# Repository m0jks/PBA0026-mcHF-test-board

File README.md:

# PBA0026-mcHF-test-board
# Test board for the mcHF radio by m0nka.

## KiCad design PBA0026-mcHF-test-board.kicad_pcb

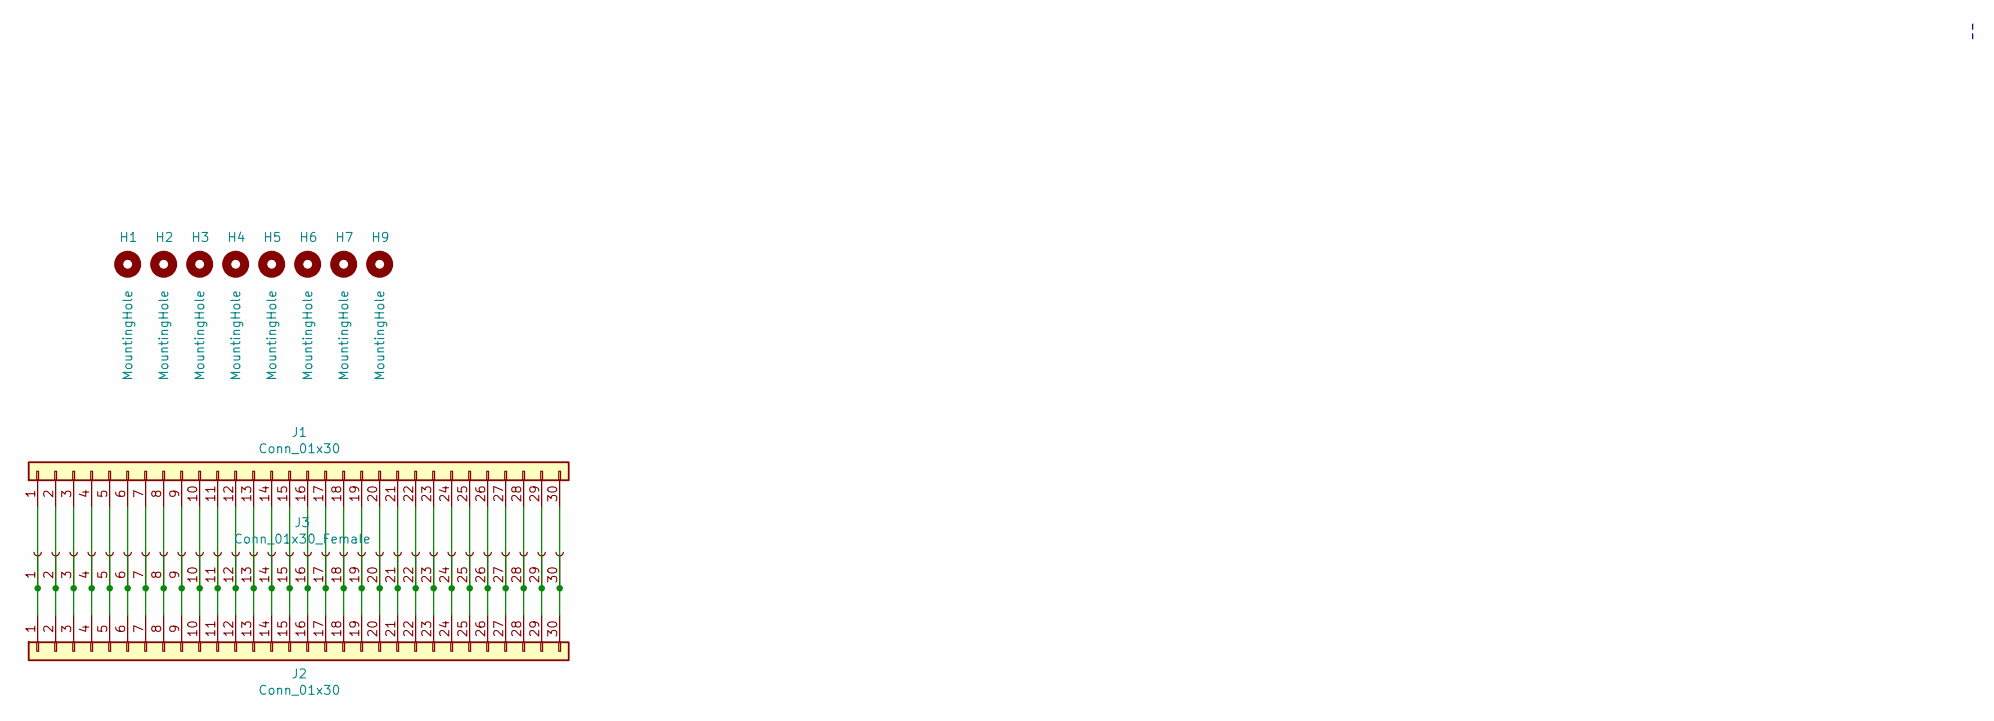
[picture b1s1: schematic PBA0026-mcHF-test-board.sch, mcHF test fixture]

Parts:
H1, H2, H3, H4, H5, H6, H7, H9: MountingHole; MountingHole_3.2mm_M3
J1: Conn_01x30; PinHeader_1x30_P2.54mm_Vertical
J2: Conn_01x30; PinSocket_1x30_P2.54mm_Vertical
J3: Conn_01x30_Female; PinSocket_1x30_P2.54mm_Vertical

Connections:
unnamed: J1.1, J2.1, J3.1
unnamed: J1.2, J2.2, J3.2
unnamed: J1.3, J2.3, J3.3
unnamed: J1.4, J2.4, J3.4
unnamed: J1.5, J2.5, J3.5
unnamed: J1.6, J2.6, J3.6
unnamed: J1.7, J2.7, J3.7
unnamed: J1.8, J2.8, J3.8
unnamed: J1.9, J2.9, J3.9
unnamed: J1.10, J2.10, J3.10
unnamed: J1.11, J2.11, J3.11
unnamed: J1.12, J2.12, J3.12
unnamed: J1.13, J2.13, J3.13
unnamed: J1.14, J2.14, J3.14
unnamed: J1.15, J2.15, J3.15
unnamed: J1.16, J2.16, J3.16
unnamed: J1.17, J2.17, J3.17
unnamed: J1.18, J2.18, J3.18
unnamed: J1.19, J2.19, J3.19
unnamed: J1.20, J2.20, J3.20
unnamed: J1.21, J2.21, J3.21
unnamed: J1.22, J2.22, J3.22
unnamed: J1.23, J2.23, J3.23
unnamed: J1.24, J2.24, J3.24
unnamed: J1.25, J2.25, J3.25
unnamed: J1.26, J2.26, J3.26
unnamed: J1.27, J2.27, J3.27
unnamed: J1.28, J2.28, J3.28
unnamed: J1.29, J2.29, J3.29
unnamed: J1.30, J2.30, J3.30

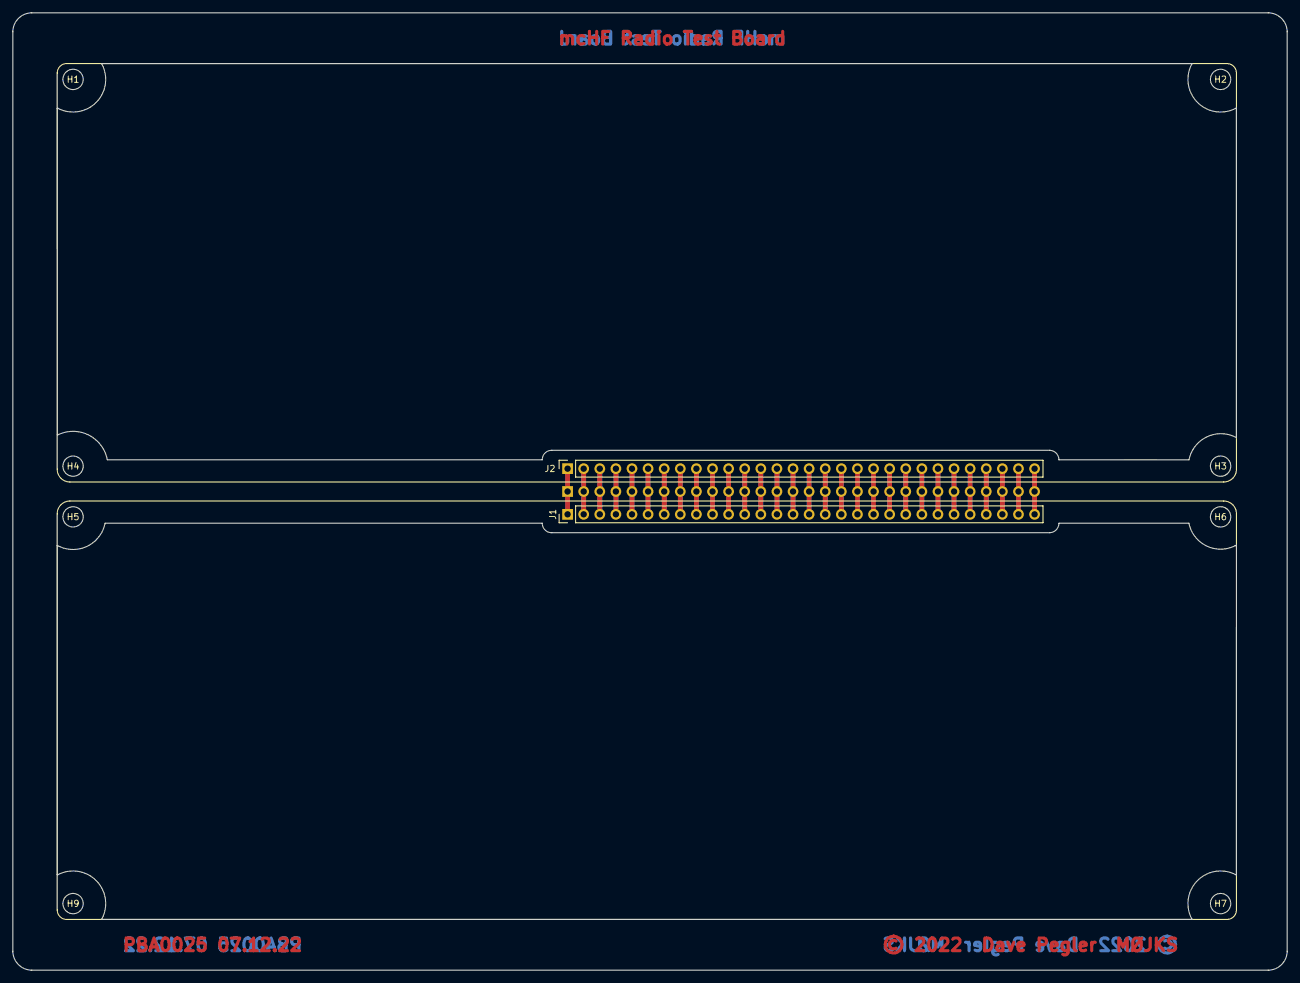
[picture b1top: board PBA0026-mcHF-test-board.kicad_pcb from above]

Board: 2 copper layers, 201.0 x 151.0 mm, 11 parts (1 on the bottom side), 30 nets.

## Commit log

2022-12-10 Add test board schematics and PCB for the mcHF amateur radio transceiver. This PCB allows the mcHF UI and RF board to be opened up, giving access to both sides of both boards

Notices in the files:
PBA0026-mcHF-test-board.kicad_pcb:
© 2022  Dave Pegler  MØJKS
